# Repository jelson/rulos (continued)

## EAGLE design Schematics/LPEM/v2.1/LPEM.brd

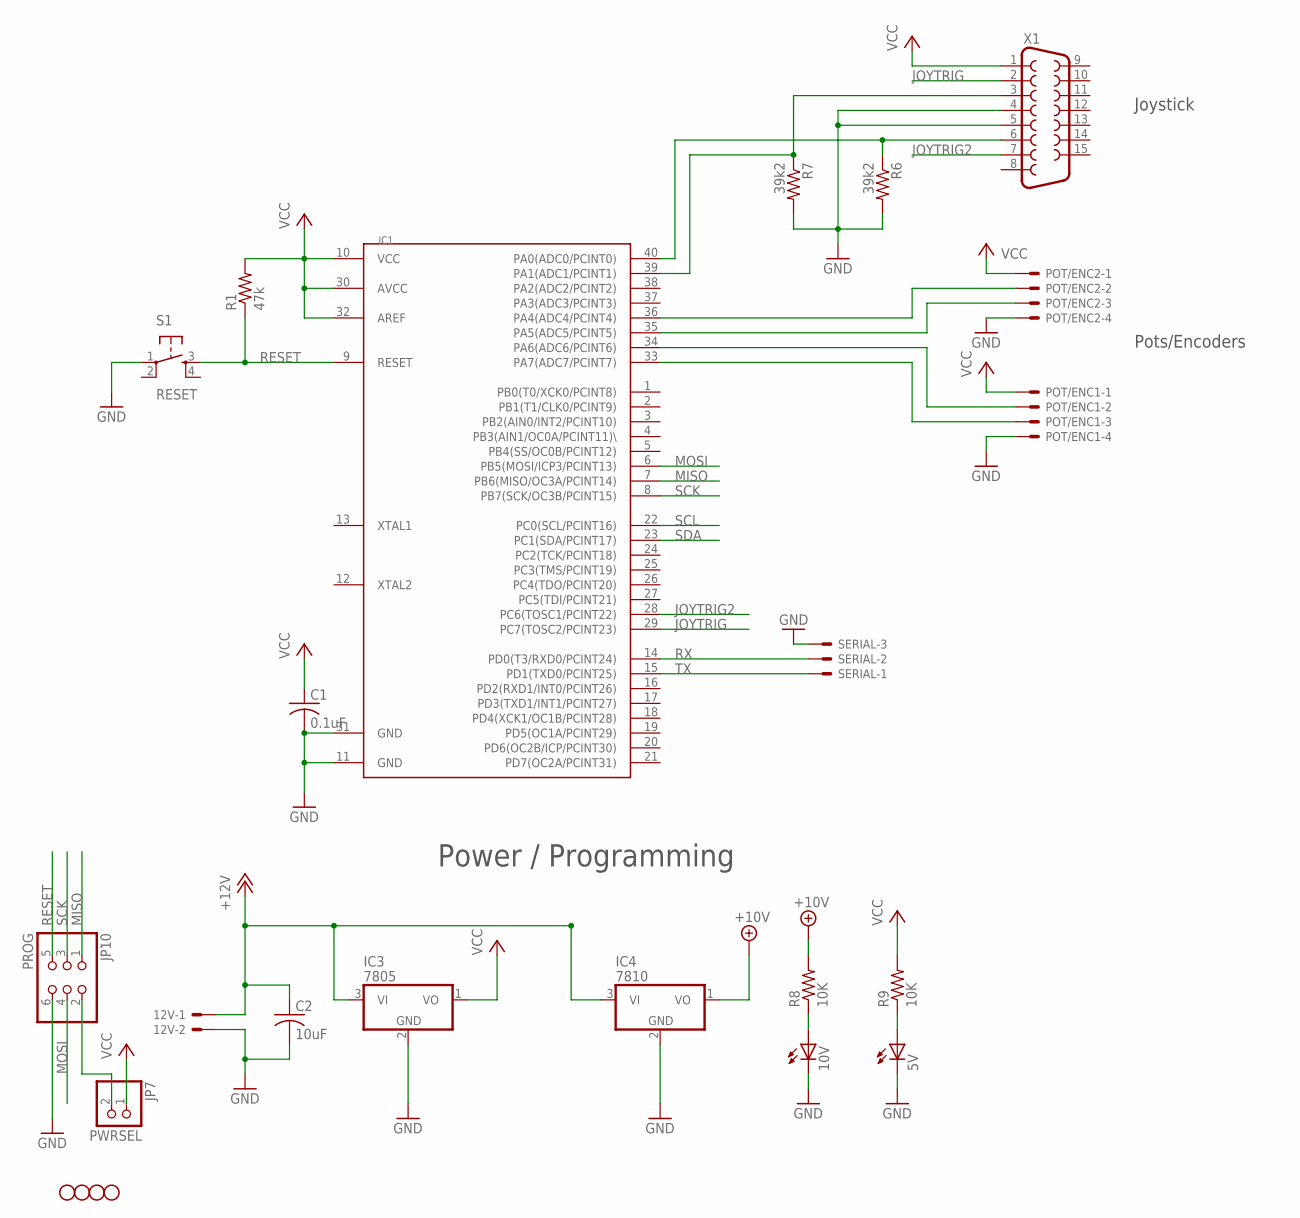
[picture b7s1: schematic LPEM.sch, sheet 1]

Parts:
5V, 10V: LED3MM
12V: 22-23-2021
C1: 0.1uF; C025-025X050
C2: 10uF; C025-025X050
IC1: MEGA1284P; DIL40
IC3: 7805; TO92
IC4: 7810; TO92
JP1, JP2, JP8, JP9: STAND-OFF
JP7: PWRSEL; 1X02
JP10: PROG; 2X03
POT/ENC1, POT/ENC2: 22-23-2041
R1: 47k; 0204/5
R6, R7: 39k2; 0204/5
R8, R9: 10K; 0204/5
S1: RESET; TACTILE-PTH
SERIAL: 22-23-2031
X1: F15HP

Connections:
+10V: IC4.1 (VO), R8.2; also elsewhere on the board
+12V: 12V.1, C2.1, IC3.3 (VI), IC4.3 (VI); also elsewhere on the board
GND: 5V.K (C), 10V.K (C), 12V.2, C1.2, C2.2, IC1.11 (GND), IC1.31 (GND), IC3.2 (GND), IC4.2 (GND), JP10.6, POT/ENC1.4, POT/ENC2.4, R6.2, R7.2, S1.1, SERIAL.3, X1.4, X1.5; also elsewhere on the board
JOYTRIG: IC1.29 (PC7(TOSC2/PCINT23)), X1.2
JOYTRIG2: IC1.28 (PC6(TOSC1/PCINT22)), X1.7
MISO: IC1.7 (PB6(MISO/OC3A/PCINT14)), JP10.1
MOSI: IC1.6 (PB5(MOSI/ICP3/PCINT13)), JP10.4
unnamed: IC1.35 (PA5(ADC5/PCINT5)), POT/ENC2.3
unnamed: IC1.36 (PA4(ADC4/PCINT4)), POT/ENC2.2
unnamed: IC1.39 (PA1(ADC1/PCINT1)), R7.1, X1.3
unnamed: JP7.2, JP10.2
unnamed: 5V.A, R9.1
unnamed: IC1.40 (PA0(ADC0/PCINT0)), R6.1, X1.6
unnamed: 10V.A, R8.1
unnamed: IC1.34 (PA6(ADC6/PCINT6)), POT/ENC1.2
unnamed: IC1.33 (PA7(ADC7/PCINT7)), POT/ENC1.3
RESET: IC1.9 (RESET), JP10.5, R1.1, S1.3
RX: IC1.14 (PD0(T3/RXD0/PCINT24)), SERIAL.2
SCK: IC1.8 (PB7(SCK/OC3B/PCINT15)), JP10.3
SCL: IC1.22 (PC0(SCL/PCINT16)); also elsewhere on the board
SDA: IC1.23 (PC1(SDA/PCINT17)); also elsewhere on the board
TX: IC1.15 (PD1(TXD0/PCINT25)), SERIAL.1
VCC: C1.1, IC1.10 (VCC), IC1.30 (AVCC), IC1.32 (AREF), IC3.1 (VO), JP7.1, POT/ENC1.1, POT/ENC2.1, R1.2, R9.2, X1.1; also elsewhere on the board

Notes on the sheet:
Power / Programming
Joystick
Pots/Encoders

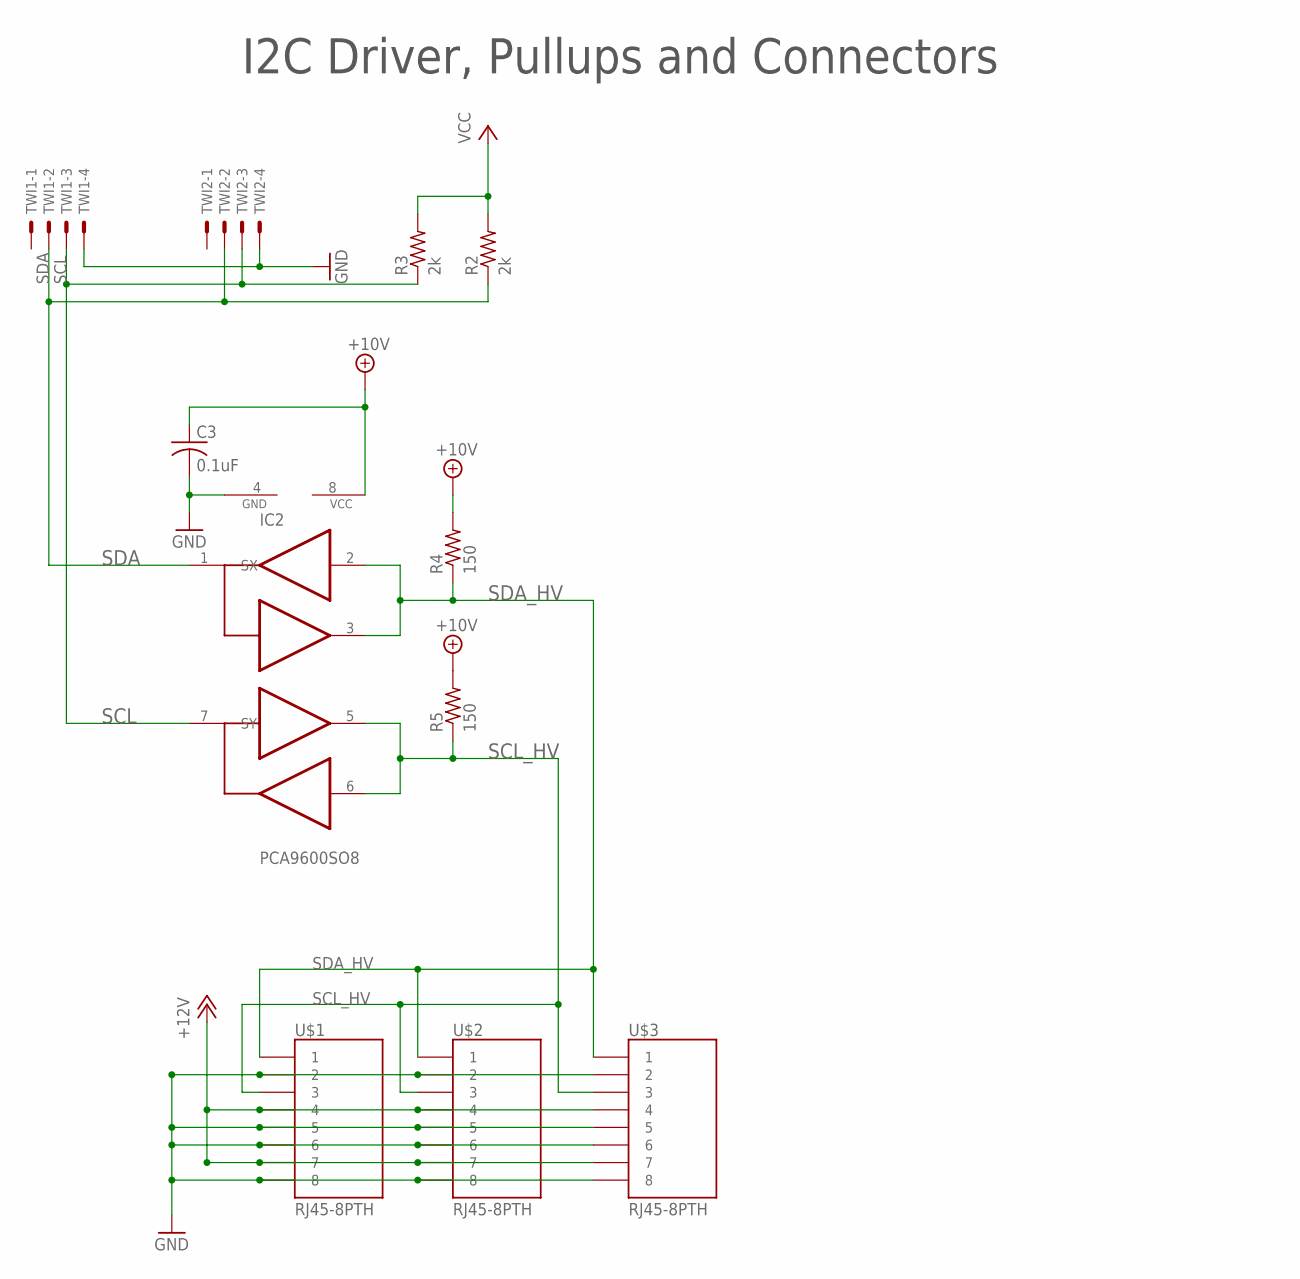
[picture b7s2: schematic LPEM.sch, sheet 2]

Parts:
C3: 0.1uF; C025-025X050
IC2: PCA9600SO8; SO08
R2, R3: 2k; 0204/5
R4, R5: 150; 0204/5
TWI1, TWI2: 22-23-2041
U$1, U$2, U$3: RJ45-8PTH; RJ45-8

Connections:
+10V: C3.1, IC2.8 (VCC), R4.2, R5.2; also elsewhere on the board
+12V: U$1.4, U$1.7, U$2.4, U$2.7, U$3.4, U$3.7; also elsewhere on the board
GND: C3.2, IC2.4 (GND), TWI1.4, TWI2.4, U$1.2, U$1.5, U$1.6, U$1.8, U$2.2, U$2.5, U$2.6, U$2.8, U$3.2, U$3.5, U$3.6, U$3.8; also elsewhere on the board
SCL: IC2.7 (SY), R3.1, TWI1.3, TWI2.3; also elsewhere on the board
SCL_HV: IC2.5 (TY), IC2.6 (RY), R5.1, U$1.3, U$2.3, U$3.3
SDA: IC2.1 (SX), R2.1, TWI1.2, TWI2.2; also elsewhere on the board
SDA_HV: IC2.2 (RX), IC2.3 (TX), R4.1, U$1.1, U$2.1, U$3.1
VCC: R2.2, R3.2; also elsewhere on the board

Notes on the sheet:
I2C Driver, Pullups and Connectors

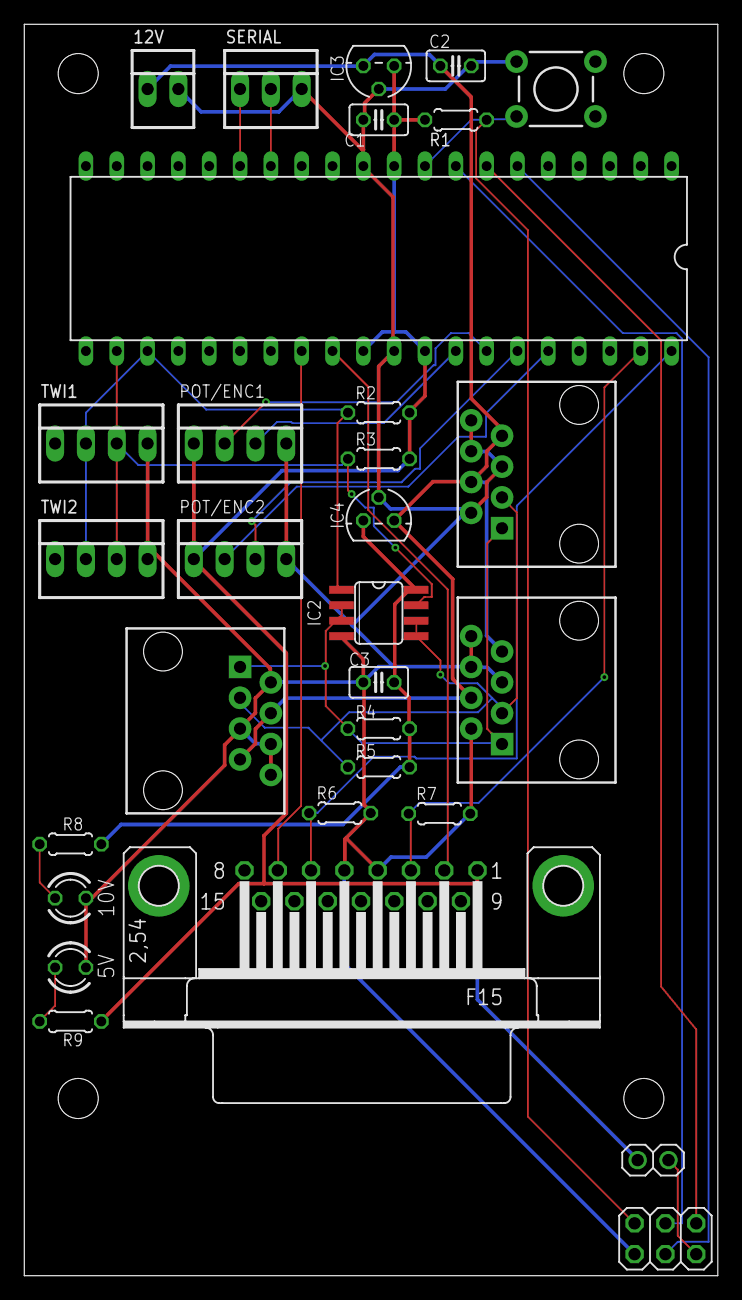
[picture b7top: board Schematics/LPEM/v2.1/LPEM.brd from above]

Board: 2 copper layers, 57.1 x 103.1 mm, 35 parts (0 on the bottom side), 25 nets.

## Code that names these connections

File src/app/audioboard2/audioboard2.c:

/*
 * Copyright (C) 2009 Jon Howell (jonh@jonh.net) and Jeremy Elson
 * (jelson@gmail.com).
 *
 * This program is free software: you can redistribute it and/or modify
 * it under the terms of the GNU General Public License as published by
 * the Free Software Foundation, either version 3 of the License, or
 * (at your option) any later version.
 *
 * This program is distributed in the hope that it will be useful,
 * but WITHOUT ANY WARRANTY; without even the implied warranty of
 * MERCHANTABILITY or FITNESS FOR A PARTICULAR PURPOSE.  See the
 * GNU General Public License for more details.
 *
 * You should have received a copy of the GNU General Public License
 * along with this program.  If not, see <https://www.gnu.org/licenses/>.
 */

#include "core/rulos.h"
#include "periph/fatfs/ff.h"

/*
 * PIN MAPPINGS:
 *
 * STM32F303CB   STM32Func  AK4430    AudioFunction
 * -----------   ---------- -------   --------------
 * 29/PA8  AF5   I2S2_MCK      4           MCLK
 * 26/PB13 AF5   I2S2_CK       5           BICK
 * 28/PB15 AF5   I2S2_SD       6           SDTI
 * 25/PB12 AF5   I2S2_WS       7           LRCK
 */

//////////////////////////////////////////////////////////////////////////////

#define NUM_SAMPLES 4096

typedef struct {
  uint8_t i2s_storage[I2S_STATE_SIZE(SAMPLE_BUF_COUNT)];
  i2s_t* i2s;
  FATFS fatfs;
  FIL fp;
  bool file_open;
} AudioState;

static void fill_buffer_cb(void* user_data, int16_t* buffer_to_fill) {
  AudioState* as = (AudioState*)user_data;
  UINT bytes_read;
  int retval =
      f_read(&as->fp, buffer_to_fill, SAMPLE_BUF_COUNT * 2, &bytes_read);
  if (retval != FR_OK) {
    LOG("read error reading from %s: %d", FAT_FILE, retval);
    __builtin_trap();
  }
  i2s_buf_filled(as->i2s, buffer_to_fill, bytes_read / 2);
}

static void audio_done_cb(void* user_data) {
  LOG("audio done");

  AudioState* as = (AudioState*)user_data;
  f_close(&as->fp);
  as->file_open = false;

  schedule_us(2000000, start_audio, user_data);
}

int main() {
  hal_init();
  init_clock(10000, TIMER1);

#ifdef LOG_TO_SERIAL
  HalUart uart;
  hal_uart_init(&uart, 115200, true, /* uart_id= */ 0);
  LOG("Log output running");
#endif

  AudioState as;
  memset(&as, 0, sizeof(as));
  
  as.i2s = i2s_init(SAMPLE_BUF_COUNT, 50000, /*user ptr*/ &as,
        fill_buffer_cb, audio_done_cb, as.i2s_storage, sizeof(as.i2s_storage));
  
  init_i2s(&as);
  init_samples(&as);

#if 1
  int num = 0;
  while (true) {
    num++;
    // LOG("iteration %d", num);
    if (HAL_I2S_Transmit(&as.i2s_handle, (uint16_t*)as.buffer, NUM_SAMPLES,
                         HAL_MAX_DELAY) != HAL_OK) {
      __builtin_trap();
    }
  }
#endif

  Network net;
  // TODO why is the network speed (200) a hard-coded magic constant!?
  init_twi_network(&net, 200, AUDIO_ADDR);

  schedule_us(10000, start_read, NULL);
  cpumon_main_loop();

  return 0;
}

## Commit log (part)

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2022-03-11 refactor startup behavior of dataloggers
2022-03-11 format
2022-03-12 Clean up some build system path handling that caused a bug in map file output filename
2022-03-15 make linereader buffer longer for datalogger
2022-03-16 autoformat
2022-03-23 add esp32 blink example
2022-03-25 for ltetag only blink led if flash is working and psoc has sent us something
2022-04-03 simpler esp32 hello world
2022-04-03 Add general mechanism for passing env vars as compiler ifdefs
    Allow env var to specify default NTP server for esp32 ntp client
2022-04-03 Switch esp32 uart tx driver to use IDF API and builtin uart driver (with its ring buffer) rather than poking at bare registers
2022-04-04 first cut at rx for esp32 uart
2022-04-04 improve the esp32 uart rx: no more polling, no more rx delay!! boom!
2022-04-04 Add linereader example program
2022-04-05 gemini datalogger: change gemini serial port baud rate to 115200
2022-04-05 dataloggers: only sync to flash every 30 sec
2022-04-07 print version on startup
2022-04-07 timestamper: generalize divider code; add support for channel 2. boom!
2022-04-13 Add pms5003 driver and test program
2022-04-13 improvements to uart test programs
2022-04-16 Update STM32G0 support libraries to latest version
2022-04-17 aqi sensor: add cache; add ntp
2022-04-17 Get data upload working
2022-04-17 Cleanups
2022-04-17 Rename cert from lectrobox to X3, since that's what it is
2022-04-17 rename files for consistency
2022-05-01 Refactor esp32 https client to do session reuse
2022-05-04 Temporarily disable gps and modem logging for ltetag datalogger
2022-05-04 ignore logfiles
2022-05-29 Finally fix async https requests for esp32
    The async mode of the esp32's https library is broken. Finally get async
    requests to work right by wrapping their synchronous mode api in a thread.
2022-05-30 Add programmer helper script for duktig
2022-05-31 Fix path of map filename
2022-06-02 Add watchdog module
2022-06-02 AQI sensor: reboot if 3 minutes have elapsed without a successful upload
2022-06-09 esp32: when an https request fails, destroy and re-create the client
    some failures leave the client object in a state that it never recovers from, so
    create a new client from scratch on each failure just in case
2022-08-17 Add gpio reads and hal_delay_ms to esp32 HAL
2022-08-17 Add DHT22 sensor driver
2022-08-17 ESP32 AQI sensor: refactor data cache; implement DHT22 version
2022-08-19 Fix some bugs in the morse code library
    * Missing comma in the character definition array after V meant V-Z were being
    transmitted incorrectly, sigh
    * Switch logical bool to using bool type instead of uint8_t
2022-08-19 DHT22: fix crash bug if the sensor times out
    If certain steps timed out, the library would return without reenabling
    interrupts.
2022-08-19 Add API to wifi library to indicate whether wifi is connected
2022-09-30 adjustments for single-port Apollo logger
2022-10-21 Fixes for newer version of gcc
    * Apparently "a - b > 0" is UB if the result generates rollover, which is what
    our clock comparison algorithm uses. Rewritten with more complex but defined
    behavior.
    * Added new time_delta function to determine by how much two timestamps are
    separated, taking into account rollover considerations.
    * Added some unit tests
2022-10-21 Another attempt at making time comparisons nicer
    The previous commit stopped relying on overflow math entirely.
    Now I've learned that math overflow is well defined for unsigned types,
    just not signed types, so I'm using that to simplify the code a bit.
2022-10-21 Fix memory bug in stm32 uart rx in interrupt mode
    Interrupt mode of stm32 uart rx had a bug: if the incoming rx buffer overflows,
    we record that data was lost but then we don't actually lose the data. We just
    keep on writing past end of buffer.
2022-10-21 Updates to stm32g0 uart support
    * Rearrange assignment of DMA channels to favor RX. This is a stupid patch until
    I finally have time to finish dynamic DMA channel assignment.
    * Add support for USART1 on B7/B6
    * Reduce load (in exchange for slight latency increase) - don't flush rx buffer
    when prior one is done. i.e., wait until the idle interrupt (or rx buf full
    signal) causes a flush
2022-10-21 Create SoloListener variant of datalogger
2022-10-23 duktig programmer: enable target power
2022-10-24 Refactor datalogger to be faster
    Dataloggers were still dropping rx data. Improve speed by
    * reducing buffer copies
    * don't sync fat on every write, but periodically
    * stop printing verbose output to console
2022-10-25 Refactor stm32 uart pin assignment code
    Some weird preprocessor magic was required but it makes the specification of
    uarts to pins a lot easier and more consistent to use
2022-10-25 less flashing on solo-logger
    flash one led every 30s: the orange one if there was new data
    written, the green one if there wasn't
2022-11-01 Rename 'datalogger' to 'gps-test-rig'
2022-11-01 Use ccache if available
2022-11-01 stm32 uart: Reactivate servicing outstanding idle interrupts
    Verified uart on datalogger still does not drop data
2022-12-14 Fix duktig bug exposed by newer compiler
2022-12-14 Adjust duktig programming script
2023-03-04 datalogger: generalize data processor; check in new dataset
2023-03-04 datalogger: add post processed maps from datalogger
2023-03-27 Various fixups and generalizations to gps test rig firmware
2023-03-27 Fix bug preventing clock from being monotonic
2023-03-31 improve pps plotting script
2023-04-18 Improve pps eval script
2023-05-24 Timestamper improvements
    * Add monotonicity check
    * Remove obsolete self-test code
    * Better statistics collection
2023-06-02 Use the tvb split-highorder-bits technique to avoid monotonicity problems
2023-07-06 Put timestamper back into normal mode rather than monotonicity-test mode
2023-08-16 change balloon light timeout
2023-09-07 trivial: add null param for non-cb uart-init calls
2023-10-16 Update to latest stm32 libraries
2023-10-16 gd32 wip
2023-10-22 Web site updates
2023-11-01 Change build system to support out-of-tree (ext) peripherals
    Also, a few more steps towards compiling USB support for stm32; incomplete
2023-11-08 Update reference to Media repo
2023-11-08 Change how arm gcc is found
2023-12-05 bug fix to code that finds arm gcc path
2023-12-07 switch duktig programmer to use gdb-multiarch
2024-01-01 empty file for doorbell
2024-01-01 knobs for selecting UART
2024-01-01 rename xline
2024-01-01 cpumon_main_loop becomes scheduler_run
2024-02-05 Fix stm32 UART crash bug
    Crashes if an rx-data-ready interrupt is received on a uart not configured to
    receive. The receive buffer is NULL so causes a segv.
2024-04-21 Add support for GPIO Port F for stm32
2024-05-01 timestamper: update LED pin for test5 board
2024-07-22 WIP changes to support new datalogger.
2024-07-23 Commit WIP with working I2C and logging
2024-07-24 Initial current calibration values.
2024-08-13 Updates for range selection and BOOT0 option bit setting.
2024-08-20 Update AVR timer code to be less hacky, avoid complaints from newer GCCs
2024-10-16 Add STM32C0 repo to ext/stm32
2024-10-16 Initial (untested) support for STM32C0
2024-11-20 Port duktig to STM32C0
2024-11-23 Increased DMA buffer to eliminate logging dropouts
2024-11-26 address dropped bytes
    i had a theory that dropped bytes were caused by an asynchronous buffer swap that was not well aligned to the arrival of the next byte. i added a loop to spin until the next byte, which seems to fix 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
2025-01-19 Honor locally set paths when building
2025-01-19 add clarifying comment
2025-01-19 Update STM32C0 library version
2025-10-22 update stm32c0 libraries
2025-10-22 usb test update
2025-10-24 First working version of native stm32 USB DCD device support!
2025-10-24 vscode settings: ignore files in ext/
2025-10-24 Remove unused libusb_stm32 library
2025-10-24 Update all stm32 support libraries to their latest versions
2025-10-25 Refactor STM32 native USB CDC support into a RULOS peripheral
2025-12-12 Run the USB tx completion callback from "user space", not at interrupt time
2025-12-12 First USB version of timestamper!!
    * Switch output to be via USB rather than UART
    * Switch timestamp buffer to be circular buffer rather than ping-pong
    * Ruthlessly optimize the number of cycles in the ISR to reduce dead time; reduced from 75 to 48 cycles (441 to 282ns through static analysis; real world dead time testing still required)
2025-12-31 create CACHEDIR.TAG in build directory
2026-02-26 Add 'spinner' style output to builds
    Make builds use less screen space by using the scons spinner
2026-02-27 Timestamper resilience to failed HSE oscillator
    * On startup, set a timeout on HSE startup so that it fails in a timely manner rather than hanging. (Bug fix: increment HAL tick on each SysTick)
    * If HSE startup succeeds, use clock security system to catch clocks that later fail
    * If clock fails either at init or during operation via CSS, set a new global indicating the clock has failed
    * Timestamper: watch for this clock failure indication and print a message, and flash error LEDs, rather than just hanging
2026-02-28 tiny cleanup of usbd_cdc
    clear tx_in_flight buffer when no buffer is in flight.
    not really a bug, just good hygeine and makes debugging easier
2026-02-28 Timestamper: better USB debug output
    * Wait for USB host to connect before printing welcome message
    * Print notifications that pulses were missed due to buffer overflow or overcapture
2026-02-28 timestamper: fix overcapture detection
2026-03-03 Timestamper: bigger USB tx buffers
    I was previously sending only 64 bytes to the USB stack a time, because USB
    packets are 64 bytes. Turns out this was inefficient--if the stack has only 64
    bytes, it only does a single bulk data transfer per USB frame. Now we give it 1k
    at a time so we can do multiple bulk transfers per frame.
2026-03-31 update submodule config
2026-04-04 Update media git repo URL
2026-04-12 vscode config update
    Don't open submodules, since the repo has dozens from stm32
2026-04-13 build: cache git/which shell-outs and use MD5-timestamp decider
    commit_hash() and repo_is_dirty() were being invoked twice per target
    (once each for CCFLAGS and LINKFLAGS), forking a fresh 'git describe
    --dirty' every time. The --dirty flag makes git stat every tracked file,
    which became noticeably slow. Memoize both so they run once per scons
    invocation. Same treatment for which(), which also now uses shutil.which
    instead of forking /usr/bin/which.
2026-04-13 build: add canary_platforms() helper, use it across test canaries
    Introduce build_tools.canary_platforms(), which returns one
    representative chip per family RULOS knows about — one per STM32 chip
    line (e.g. g431, g474, f103 — not per density/package), one per AVR
    family (atmega32/328/1284 + attiny84/85), plus ESP32. Callers can
    narrow the scope (stm32_families, include_atmega/attiny/esp32) and
    append specific chips via extras=[...] for hardware test jigs.
2026-04-13 uart: add linecounter RX-drop torture test + canary ram/flash selection
    linecounter is a silent RX-drop detector: receive fixed-length lines
    via linereader, establish expected length from the first line, count
    mismatches, and emit a single periodic summary (lines, length
    mismatches, linereader overflows, bytes/sec averaged over the run).
    No per-line output, so TX backpressure can't induce RX drops itself.
    write.py now takes a line count argument and produces 100-char padded
2026-04-13 uart: stream write.py output in chunks instead of buffering in RAM
    Build ~4KB of lines at a time and write each chunk, keeping peak host
    RAM bounded regardless of num_lines. Kept the binary-mode fd +
    buffering=0 to avoid line-buffered TTY flushing on every '\n', which
    is what capped throughput before.
2026-04-13 canary: include simulator by default, make test programs build on it
    canary_platforms() now defaults include_sim=True so every canary SConstruct
    exercises a host-simulator build alongside the embedded targets. The twi
    canary opts out (twi_tests sits on an F3-specific driver path; not worth
    the ergonomic cost of a sim branch in twi.c for canary coverage).
    test-pin.h now owns the cross-platform gpio abstraction: it pulls in
    core/hardware.h on real targets and provides no-op gpio_* stubs plus a
2026-04-17 audoiboard: serial port baud rate to 1M
2026-04-30 first version of pulse generator, untested
